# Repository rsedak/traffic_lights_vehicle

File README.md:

[Croatian version](README_HR-HR.md).

Introduction
============

Traffic lights for vehicle shield is version of Arduino Uno based shield for student education.

Contributors
------------
- Robert Sedak — features, Arduino programming, schematic design, CAD design.

Application
-----------
Robert Sedak made a video with example programmed in Arduino IDE:

You can download example for Arduino IDE from [here](examples/).

Bill Of Materials
-----------------
- 1 ea., PCB
- 3 ea., 330 ohm 1/4W 1% Resistor (R1, R2, R3)
- 1 ea., LED 3mm - Red (D1)
- 1 ea., LED 3mm - Yellow (D2)
- 1 ea., LED 3mm - Green (D3)
- 1 ea., 1x4Pin 2.54mm Right Angle Pin Header - Black

Design Files
------------
This project is designed using Open Source [KiCad](http://kicad.org/). Design files are located in the [design_files](design_files/) folder.  You can see the [schematic](images/traffic_lights_vehicle_schematic.png).

Gerber files
------------
You can download gerber files from [here](gerber/traffic_lights_vehicle.zip).

Firmware
--------
This project can be programmed using the Open Source [Arduino](https://www.arduino.cc/).
Arduino example is located in [examples](examples/) folder.

License
-------
[Attribution-ShareAlike 4.0 International (CC BY-SA 4.0)](https://creativecommons.org/licenses/by-sa/4.0/)

You are free to:
- Share — copy and redistribute the material in any medium or format
- Adapt — remix, transform, and build upon the material

This license is acceptable for Free Cultural Works.
- The licensor cannot revoke these freedoms as long as you follow the license terms.

Under the following terms:
- Attribution — You must give appropriate credit, provide a link to the license, and indicate if changes were made. You may do so in any reasonable manner, but not in any way that suggests the licensor endorses you or your use.
- ShareAlike — If you remix, transform, or build upon the material, you must distribute your contributions under the same license as the original.

No additional restrictions — You may not apply legal terms or technological measures that legally restrict others from doing anything the license permits.

Reference Designs ARE PROVIDED "AS IS" AND "WITH ALL FAULTS". Authors DISCLAIMS ALL OTHER WARRANTIES, EXPRESS OR IMPLIED, REGARDING PRODUCTS, INCLUDING BUT NOT LIMITED TO, ANY IMPLIED WARRANTIES OF MERCHANTABILITY OR FITNESS FOR A PARTICULAR PURPOSE.
Authors may make changes to specifications and product descriptions at any time, without notice. The Customer must notrely on the absence or characteristics of any features or instructions marked "reserved" or "undefined."
Authors reservesthese for future definition and shall have no responsibility whatsoever for conflicts or incompatibilities arising from future changes to them. The product information on the Web Site or Materials is subject to change without notice. Do not finalize a design with this info.

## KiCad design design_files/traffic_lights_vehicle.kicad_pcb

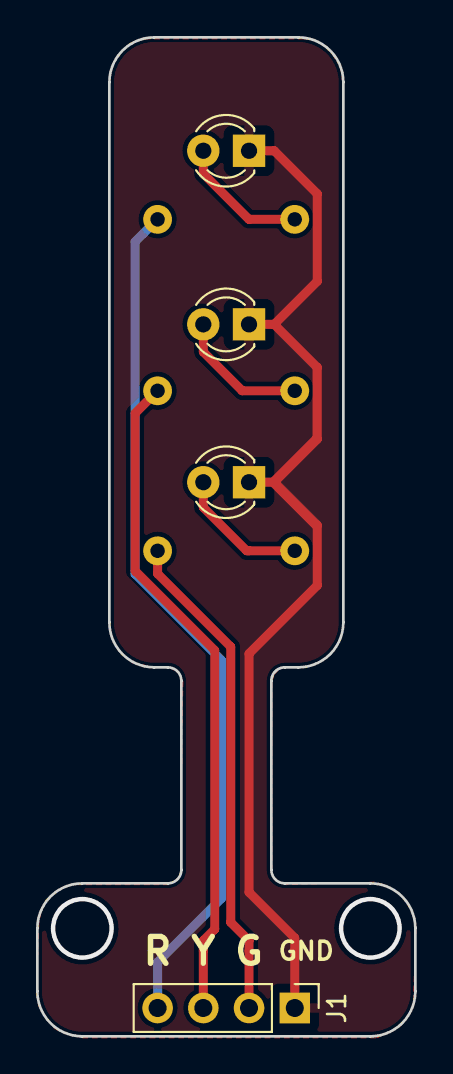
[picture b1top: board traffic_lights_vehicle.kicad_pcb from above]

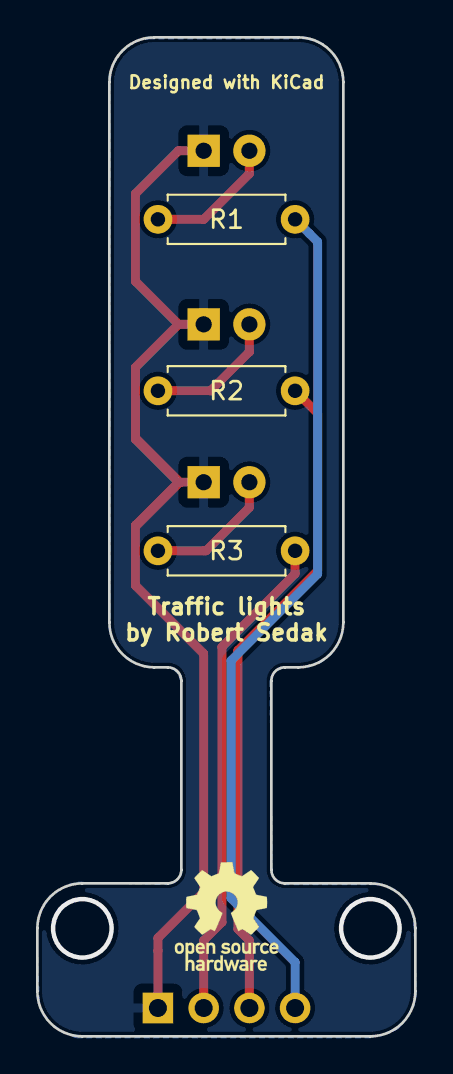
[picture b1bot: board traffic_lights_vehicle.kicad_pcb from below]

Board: 2 copper layers, 21.0 x 55.5 mm, 7 parts (3 on the bottom side), 7 nets.

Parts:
D1, D2, D3: LED; LED_D3.0mm
J1: Conn_01x04_Male; PinHeader_1x04_P2.54mm_Vertical
R1, R2, R3: 220R; R_Axial_DIN0207_L6.3mm_D2.5mm_P7.62mm_Horizontal

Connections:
unnamed: D1.1, D2.1, D3.1, J1.1
unnamed: D1.2, R1.1
unnamed: D2.2, R2.2
unnamed: D3.2, R3.1
unnamed: J1.2, R3.2
unnamed: J1.3, R2.1
unnamed: J1.4, R1.2

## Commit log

2022-11-05 Added default image for video

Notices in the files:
design_files/traffic_lights_vehicle.kicad_pcb:
License: CC-BY-SA 4.0
